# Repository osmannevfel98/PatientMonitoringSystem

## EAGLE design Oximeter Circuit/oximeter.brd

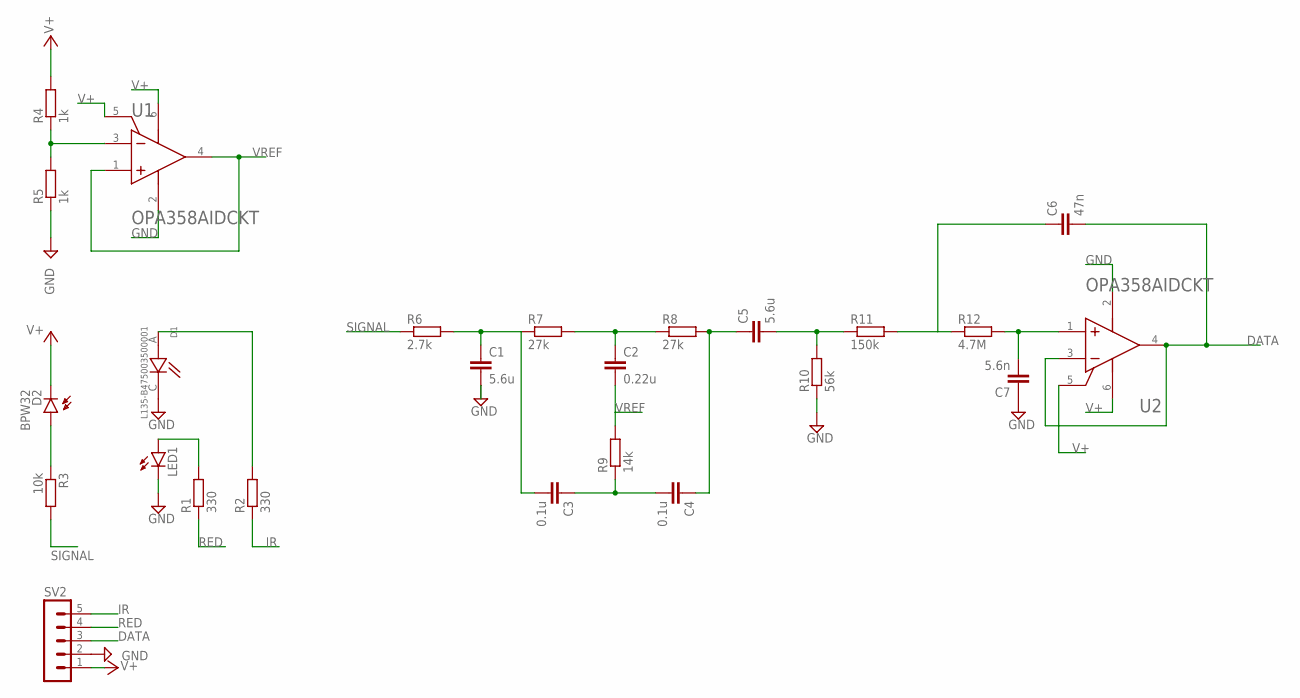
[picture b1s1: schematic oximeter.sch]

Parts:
C1, C5: 5.6u; C0603
C2: 0.22u; C0603
C3, C4: 0.1u; C0603
C6: 47n; C0603
C7: 5.6n; C0603
D1: L135-B475003500001; LED_L135-B475003500001
D2: BPW32
LED1: LEDCHIP-LED0603; CHIP-LED0603
R1, R2: 330; R0603
R3: 10k; R0603
R4, R5: 1k; R0603
R6: 2.7k; R0603
R7, R8: 27k; R0603
R9: 14k; R0603
R10: 56k; R0603
R11: 150k; R0603
R12: 4.7M; R0603
SV2: MA05-1
U1, U2: TEXAS_INSTRUMENTS_OPA358AIDCKTTEXAS_INSTRUMENTS_O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; TEXAS_INSTRUMENTS_OPA358AIDCKT_0

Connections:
DATA: C6.2, SV2.3, U2.3 (IN-), U2.4 (OUT)
GND: C1.2, C7.1, D1.C, LED1.C, R5.1, R10.1, SV2.2, U1.2 (GND), U2.2 (GND)
IR: R2.1, SV2.5
unnamed: D2.A, R3.1
unnamed: D1.A, R2.2
unnamed: LED1.A, R1.2
unnamed: R4.1, R5.2, U1.3 (IN-)
unnamed: C1.1, C3.2, R6.2, R7.1
unnamed: C2.1, R7.2, R8.1
unnamed: C7.2, R12.2, U2.1 (IN+)
unnamed: C3.1, C4.2, R9.1
unnamed: C4.1, C5.1, R8.2
unnamed: C5.2, R10.2, R11.1
unnamed: C6.1, R11.2, R12.1
RED: R1.1, SV2.4
SIGNAL: R3.2, R6.1
V+: D2.K (C), R4.2, SV2.1, U1.5 (ENABLE), U1.6 (V+), U2.5 (ENABLE), U2.6 (V+)
VREF: C2.2, R9.2, U1.1 (IN+), U1.4 (OUT)

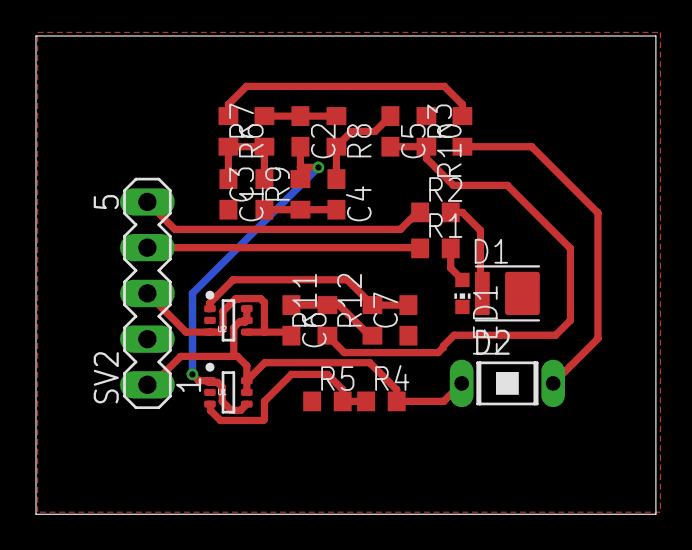
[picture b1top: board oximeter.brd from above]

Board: 2 copper layers, 34.4 x 26.6 mm, 25 parts (0 on the bottom side), 18 nets.

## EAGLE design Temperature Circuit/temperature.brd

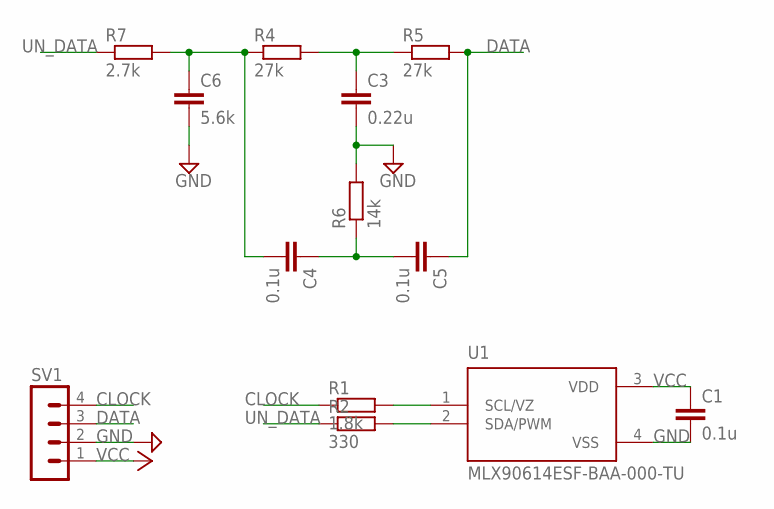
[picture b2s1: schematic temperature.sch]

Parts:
C1, C4, C5: 0.1u; C0603
C3: 0.22u; C0603
C6: 5.6k; C0603
R1: 1.8k; R0603
R2: 330; R0603
R4, R5: 27k; R0603
R6: 14k; R0603
R7: 2.7k; R0603
SV1: MA04-1
U1: MLX90614ESF-BAA-000-TU; TO254P942H425-4

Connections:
CLOCK: R1.1, SV1.4
DATA: C5.1, R5.2, SV1.3
GND: C1.2, C3.2, C6.2, R6.2, SV1.2, U1.4 (VSS)
unnamed: R1.2, U1.1 (SCL/VZ)
unnamed: R2.2, U1.2 (SDA/PWM)
unnamed: C3.1, R4.2, R5.1
unnamed: C4.1, C5.2, R6.1
unnamed: C4.2, C6.1, R4.1, R7.2
UN_DATA: R2.1, R7.1
VCC: C1.1, SV1.1, U1.3 (VDD)

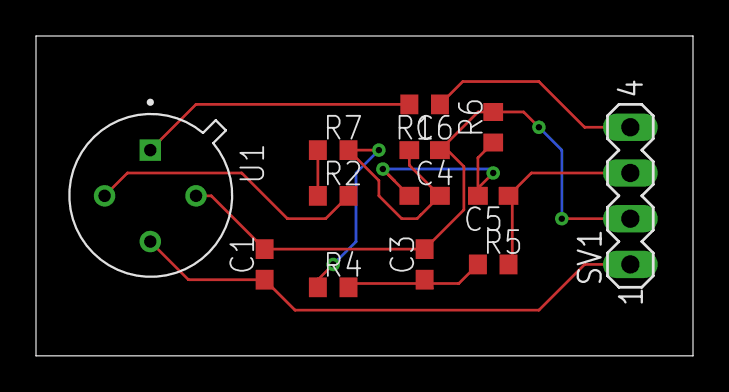
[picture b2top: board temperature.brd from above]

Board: 2 copper layers, 36.5 x 17.8 mm, 13 parts (0 on the bottom side), 10 nets.

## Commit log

2022-03-22 send
